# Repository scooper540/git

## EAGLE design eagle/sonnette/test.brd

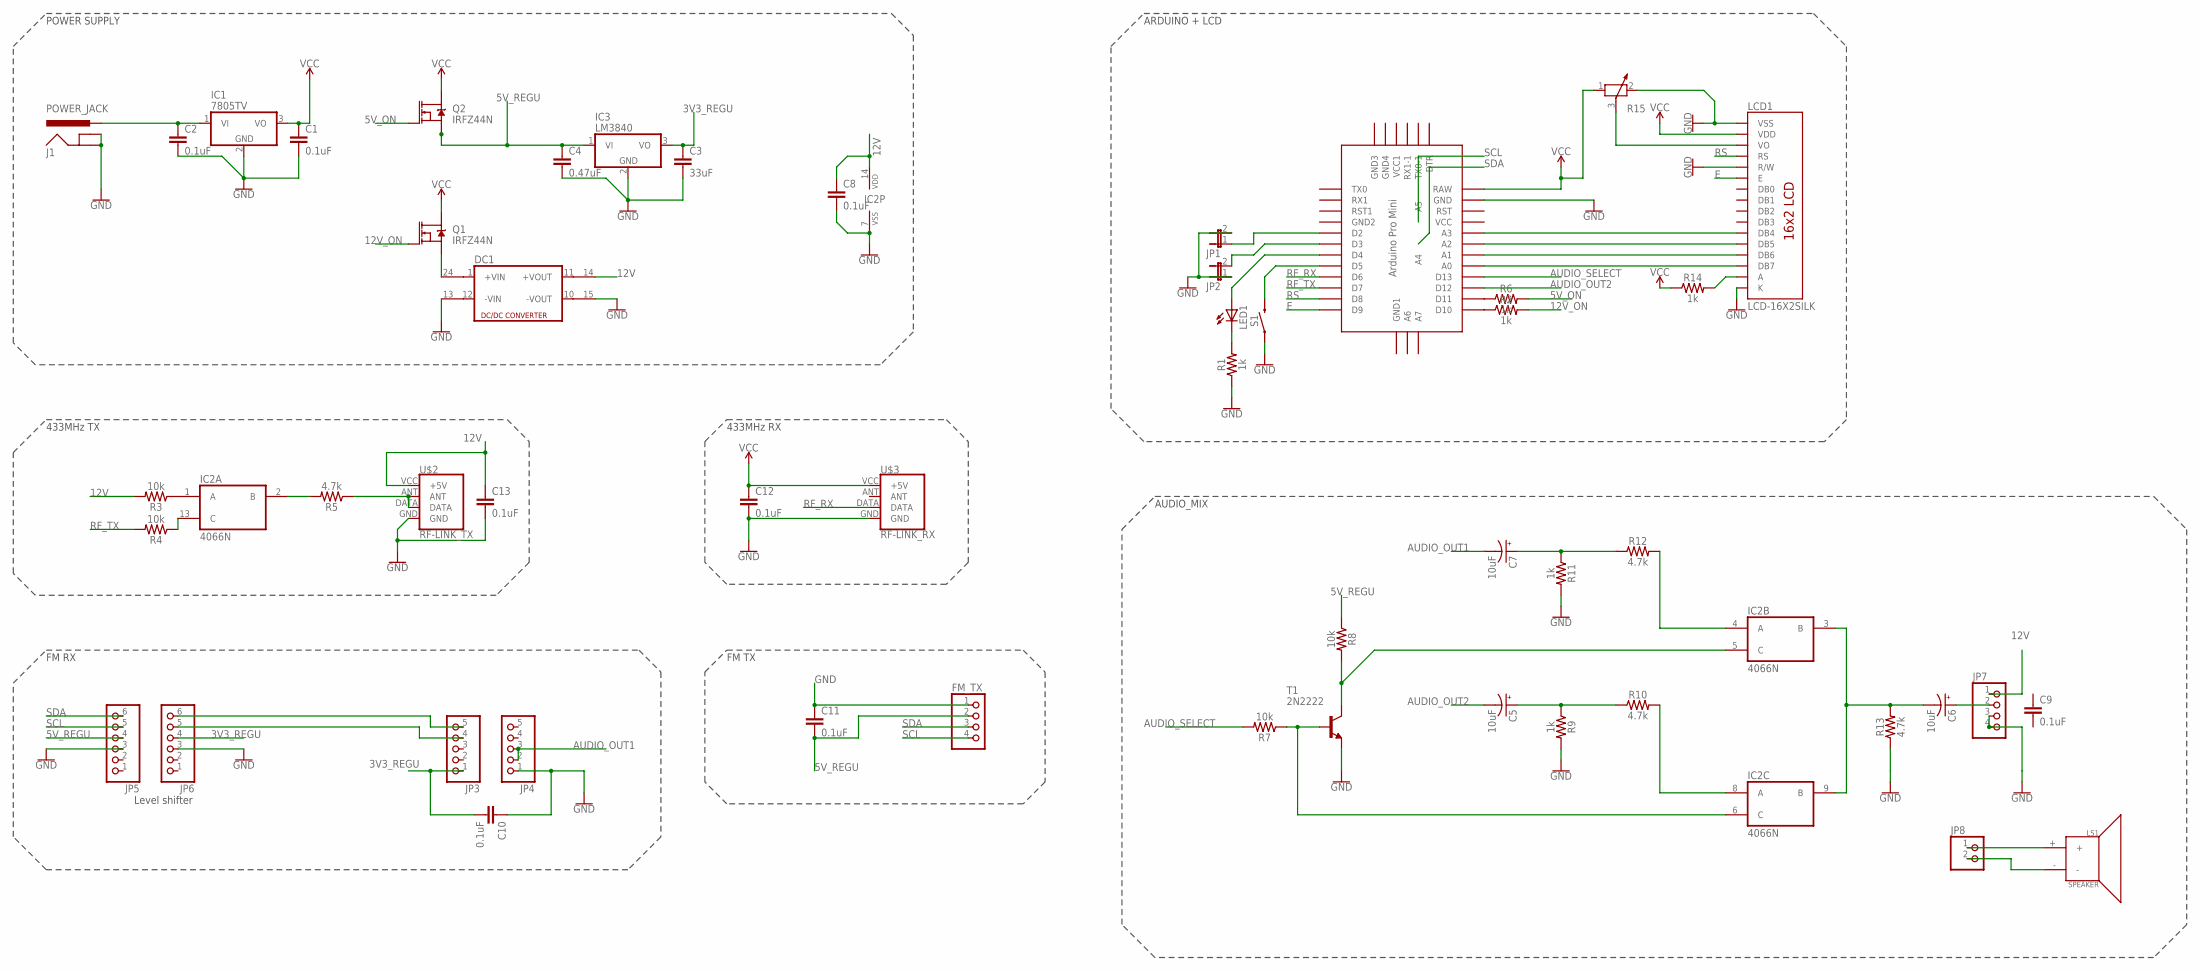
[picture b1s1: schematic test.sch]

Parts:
C1, C2, C8, C9, C10, C11, C12, C13: 0.1uF; CAP-PTH-SMALL-KIT
C3: 33uF; CAP-PTH-SMALL-KIT
C4: 0.47uF; CAP-PTH-SMALL-KIT
C5, C6, C7: 10uF; CPOL-RADIAL-2.5MM-5MM
DC1: DCW1U; DCW
FM_TX: PINHD-1X4; 1X04
IC1: 7805TV; TO220V
IC2: 4066N; DIL14
IC3: LM3840; TO220V
J1: POWER_JACK; POWER_JACK_PTH
JP1, JP2: JUMPER-2PTH; 1X02
JP3, JP4: PINHD-1X5; 1X05
JP5, JP6: PINHD-1X6; 1X06
JP7: PINHD-1X4; 1X04
JP8: PINHD-1X2; 1X02
LCD1: LCD-16X2SILK; LCD-16X2
LED1: LED3MM
LS1: SPEAKER; PCB_MOUNT_SPEAKER
Q1, Q2: IRFZ44N; TO220V
R1, R2, R6, R9, R11, R14: 1k; AXIAL-0.3
R3, R4, R7, R8: 10k; AXIAL-0.3
R5, R10, R12, R13: 4.7k; AXIAL-0.3
R15: POTENTIOMETER_PT-10; PT-10
S1: MOMENTARY-SWITCH-SPST-PTH-6.0MM; TACTILE_SWITCH_PTH_6.0MM
T1: 2N2222; TO92-EBC-OVAL
U$1: ABK-PRO-MINI
U$2: RF-LINK_TX
U$3: RF-LINK_RX; RF-LINK_TX

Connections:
3V3_REGU: C3.1, C10.2, IC3.3 (VO), JP3.1, JP6.4
5V_ON: Q2.1 (G), R6.P$2 (2)
5V_REGU: C4.1, C11.2, FM_TX.2, IC3.1 (VI), JP5.4, Q2.3 (S), R8.P$1 (1)
12V: C8.1, C13.1, DC1.14 (+VOUT1), IC2.14 (VDD), JP7.1, R3.P$2 (2), U$2.VCC (+5V)
12V_ON: Q1.1 (G), R2.P$2 (2)
AUDIO_OUT1: C7.2 (-), JP4.2, JP4.3
AUDIO_OUT2: C5.2 (-), U$1.D12
AUDIO_SELECT: IC2.6 (C), R7.P$1 (1), R7.P$2 (2), T1.B, U$1.D13
E: LCD1.6 (E), U$1.D9
GND: C1.2, C2.2, C3.2, C4.2, C8.2, C10.1, C11.1, C12.2, C13.2, DC1.13 (-VIN1), DC1.15 (-VOUT1), FM_TX.1, IC1.2 (GND), IC2.7 (VSS), IC3.2 (GND), J1.GND, J1.GNDBREAK, JP1.2, JP2.1, JP4.1, JP5.3, JP6.3, LCD1.5 (R/W), LCD1.16 (K), R1.P$1 (1), R9.P$2 (2), R11.P$2 (2), S1.1, T1.E, U$1.GND, U$2.GND, U$3.GND
unnamed: LED1.K (C), R1.P$2 (2)
unnamed: JP1.1, U$1.D2
unnamed: JP2.2, U$1.D3
unnamed: LED1.A, U$1.D4
unnamed: R2.P$1 (1), U$1.D10
unnamed: C2.1, IC1.1 (VI), J1.PWR
unnamed: DC1.24 (+VIN1), Q1.3 (S)
unnamed: IC2.13 (C), R4.P$1 (1)
unnamed: IC2.2 (B), R5.P$2 (2)
unnamed: R5.P$1 (1), U$2.ANT, U$2.DATA
unnamed: JP3.5, JP6.6
unnamed: JP3.4, JP6.5
unnamed: R6.P$1 (1), U$1.D11
unnamed: IC2.8 (A), R10.P$2 (2)
unnamed: C5.1 (+), R9.P$1 (1), R10.P$1 (1)
unnamed: IC2.5 (C), R8.P$2 (2), T1.C
unnamed: IC2.4 (A), R12.P$2 (2)
unnamed: C7.1 (+), R11.P$1 (1), R12.P$1 (1)
unnamed: JP8.1, LS1.+
unnamed: JP7.3, JP7.4
unnamed: C6.2 (-), IC2.3 (B), IC2.9 (B), R13.P$2 (2)
unnamed: C6.1 (+), JP7.2
unnamed: JP8.2, LS1.-
unnamed: IC2.1 (A), R3.P$1 (1)
unnamed: S1.3 (2), U$1.D5
unnamed: LCD1.14 (DB7), U$1.A0
unnamed: LCD1.13 (DB6), U$1.A1
unnamed: LCD1.12 (DB5), U$1.A2
unnamed: LCD1.11 (DB4), U$1.A3
unnamed: LCD1.1 (VSS), R15.2
unnamed: LCD1.15 (A), R14.P$2 (2)
unnamed: LCD1.3 (VO), R15.3
RF_RX: U$1.D6, U$3.DATA
RF_TX: R4.P$2 (2), U$1.D7
RS: LCD1.4 (RS), U$1.D8
SCL: FM_TX.4, JP5.5, U$1.A5
SDA: FM_TX.3, JP5.6, U$1.A4
VCC: C1.1, C12.1, IC1.3 (VO), Q1.2 (D), Q2.2 (D), R14.P$1 (1), R15.1, U$1.RAW, U$3.VCC (+5V)

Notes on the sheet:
POWER SUPPLY
433MHz TX
433MHz RX
FM RX
FM TX
ARDUINO + LCD
AUDIO_MIX
Level shifter

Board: 2 copper layers, 52 parts (0 on the bottom side), 48 nets, no tracks yet.

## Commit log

2017-02-22 :lollipop: Added .gitattributes & .gitignore files
2017-02-26 rx and tx working
2017-02-28 add fmrx and fmtx
2017-03-01 define PGA to 12dB bug in the library to have bigger sound output
2017-05-04 add eagle
2017-05-04 update schema for receiver
2017-05-05 updated eagle schema

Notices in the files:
parts and their libraries:
SparkFun-Retired: Licensing: Creative Commons ShareAlike 4.0 International - https://creativecommons.org/licenses/by-sa/4.0
